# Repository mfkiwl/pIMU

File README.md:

# pIMU: Unidad de medición inercial portatil

pIMU es una unidad de medición inercial (acelerómetro, giroscopio y magnetómetro) capaz de enviar los datos muestreados de forma inalámbrica. 

## Características

· Dimensiones: 18x12mm

· Tensión de trabajo: 3,5V-1V

· Consumo: 9mA (consumo optimizado en el código)

· Transmisor y protcolo: NRF24L01

· Frecuencia de emisión: 2,4GHz

## Descripción

El sensor principal encargado de la recolección de datos es un MPU9250. Éste es controlado por un microcontrolador Atmega328p que, a su vez, envía los datos en bruto a un módulo NRF24L01 para su transmisión. El regulador de tensión será un TLV61225, capaz de elevar tensiones de hasta 0,7V a los 3,3V necesarios para el funcionamiento del resto de integrados.

Este módulo está pensado para su alimentación mediante un supercondensador de tensión nominal entre 2,5V y 3,5V. Dado su bajo consumo, el uso de un supercondensador permite tiempos de uso superiores a las 2h con tiempos de carga de apenas unos segundos. 

El Atmega328p será flasheado con un el firmware Optiboot, con el fin de poder utilizar lenguaje Arduino en su programación y permitir que cualquier persona sin conocimientos de este micro concreto pueda programarlo a su gusto. La PCB cuenta con pads de soldadura suficientemente grandes asociados a los pines TX, RX y RST del microcontrolador, para poder subir sketches de forma sencilla mediante un adaptador USB-UART.  

## Instrucciones de montaje

Una vez adquiridos todos los componentes (Bill Of Materials disponible en el proyecto de Kicad), los pasos a seguir para conseguir una pIMU funcionando serán:

1. Soldadura del TLV, Atmega, sus condensadores de desacoplo y la resistencia de pull-up para el reset

2. Conexión de la interfaz SPI al ordenador. Para ello, podemos tomar como puertos de SPI los pines correspondientes al módulo NRF24L01 aún sin soldar y conectarlos a un programador ISP. En caso de no disponer de dicho programador, es posible fabricarse uno con un Arduino https://www.arduino.cc/en/Guide/ArduinoISP.

3. Cambio de los fuses (¿fusibles?) del micro. Para ello se usará el programa avrdude. Buscamos optimizar el espacio reservado al bootloader, utilizar el reloj interno a 8MHz para un menos consumo y desactivar o rebajar la detección de Brown-Out. En nuestro caso, los valores elegidos son LowFuse: 0xFF; HighFuse: 0xDE; ExtendedFuse: 0xFD. 

4. Grabado del bootloader. Existen múltiples formas de realizar este paso. La opción recomendada es hacer uso del programa de Nick Gammon https://www.gammon.com.au/bootloader. Este programa permite además cambiar los fuses de forma directa, en caso de tener problemas con avrdude en el paso anterior. La opción Lilypad 8MHz incluye ya algunas de las opciones mencionadas, como el uso de reloj interno u optimización del espacio de arranque.

5. Comprobación del bootloader. Para ello, basta soldar tres cables a los pines TX, RX y RST del pIMU, conectarlos a un conversor de USB-UART y probar a subir un sketch de Arduino (seleccionando la placa Lilypad 8MHz en caso de haber optado por esa opción en el caso anteior)

6. Soldadura del resto de componentes.

7. Programación del Atmega con el código final. Este código está disponible en este repo, e incluye la adquisicion de datos y su envío de forma periódica mediante uso de la interrupción WDT y la configuración a modo dormido del micro entre mediciones.

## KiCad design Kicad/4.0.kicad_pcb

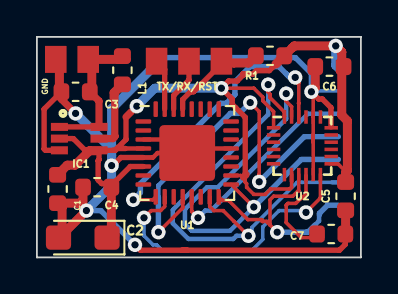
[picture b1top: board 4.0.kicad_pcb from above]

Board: 2 copper layers, 18.0 x 12.2 mm, 15 parts (1 on the bottom side), 15 nets.

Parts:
C1, C5, C7: 0.1uF; C_0603_1608Metric
C2: 4.7uF; CP_EIA-3216-18_Kemet-A
C3, C4: 10uF; C_0603_1608Metric
C6: 10nF; C_0603_1608Metric
GND: Conn_01x02_Female; ConBAT
IC1: TLV61225
L1: 4.7uH; L_0603_1608Metric
NRF24L01: Módulo NRF24L01; ConNRF_3
R1: 10K; R_0603_1608Metric
TX/RX/RST: Conn_01x03_Female; ConPRG
U1: ATmega328P-MU; QFN-32-1EP_5x5mm_P0.5mm_EP3.1x3.1mm
U2: MPU-9250; QFN-24_3x3mm_P0.4mm

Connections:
+3V3: C1.1, C2.1, C4.1, C5.1, C6.1, IC1.2, IC1.4, NRF24L01.1, R1.1, U1.4, U1.6, U1.18, U2.1, U2.8, U2.13
/CE_I: U1.9, U2.22
/CE_R: NRF24L01.3, U1.13
/CSN: NRF24L01.4, U1.12
/MISO: NRF24L01.7, U1.16, U2.9
/MOSI: NRF24L01.6, U1.15, U2.24
/SCK: NRF24L01.5, U1.17, U2.23
Earth: C1.2, C2.2, C3.2, C4.2, C5.2, C6.2, C7.2, GND.2, IC1.3, NRF24L01.2, U1.3, U1.5, U1.21, U1.33, U2.11, U2.18, U2.20
INT: U1.10, U2.12
unnamed: C7.1, U2.10
unnamed: IC1.5, L1.2
RES: R1.2, TX/RX/RST.3, U1.29
RX: TX/RX/RST.2, U1.30
TX: TX/RX/RST.1, U1.31
VCC: C3.1, GND.1, IC1.1, IC1.6, L1.1

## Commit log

2020-05-12 Añadidos Gerbers PCB
2020-05-12 Añadido código
